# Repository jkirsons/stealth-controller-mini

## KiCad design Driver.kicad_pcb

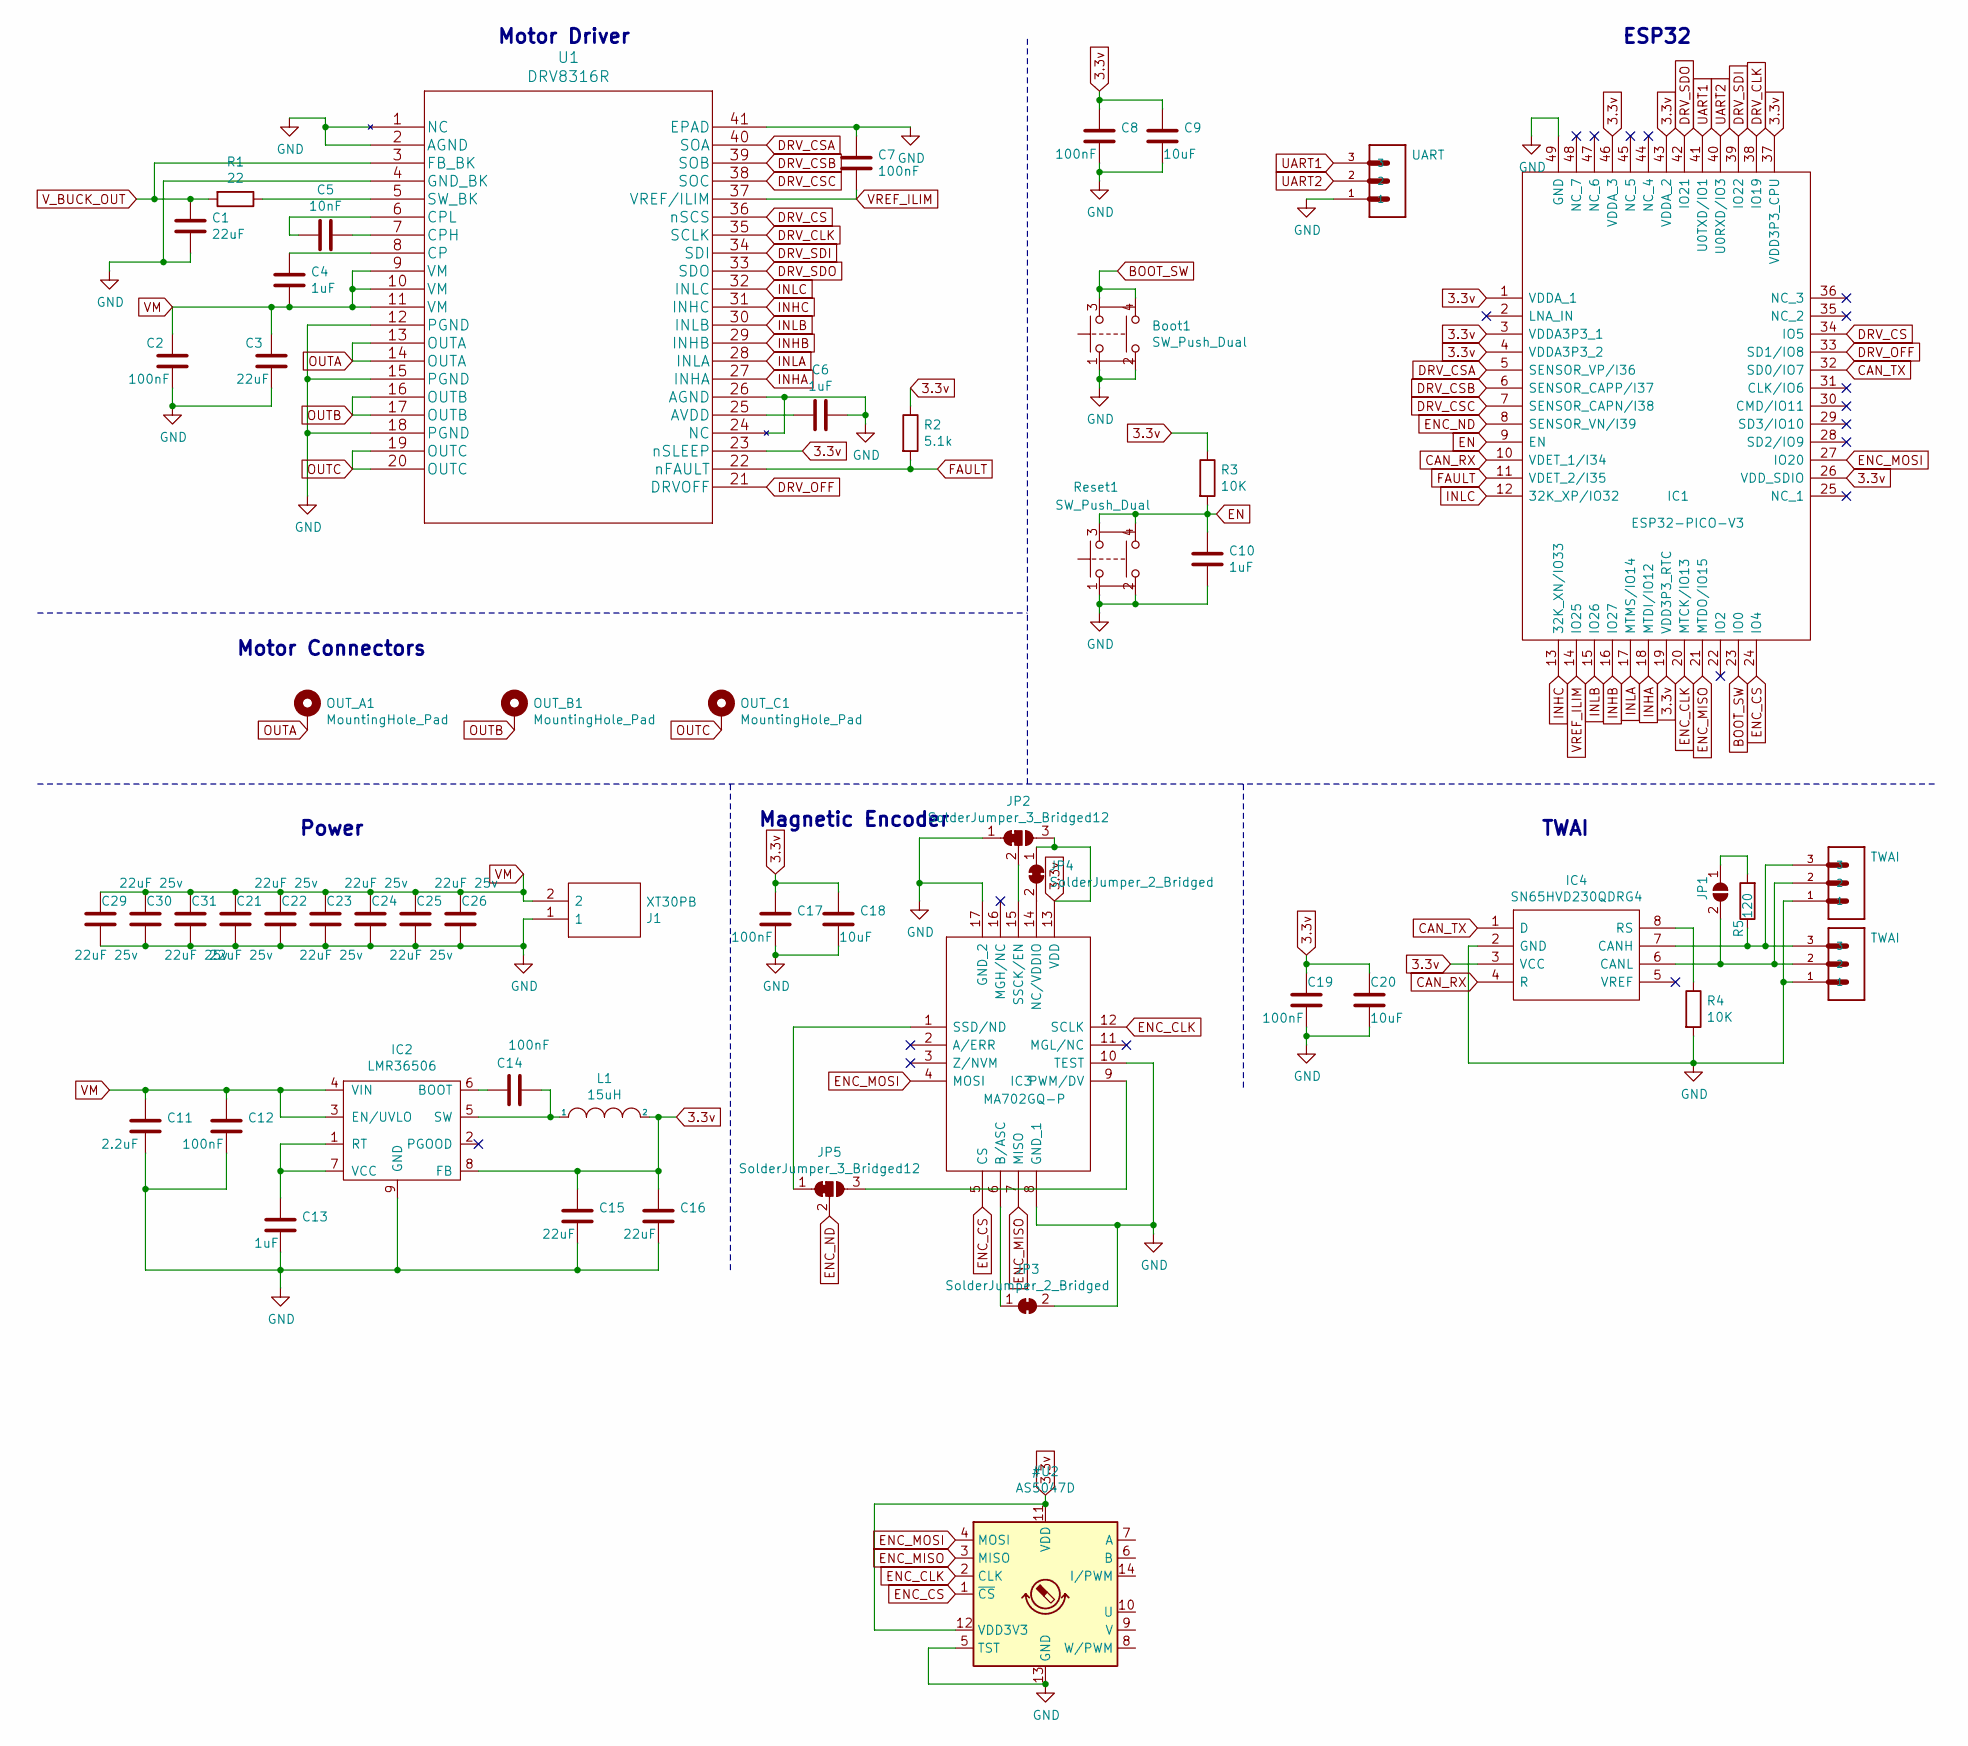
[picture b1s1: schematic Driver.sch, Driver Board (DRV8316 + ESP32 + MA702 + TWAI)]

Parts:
Boot1: SW_Push_Dual; XKB_Connectivity_TS-1177-B-B-B
C1, C15, C16: 22uF; C_0603_1608Metric
C2, C7, C8, C12, C14, C17, C19: 100nF; C_0603_1608Metric
C3: 22uF; C_0805_2012Metric
C4, C6, C10, C13: 1uF; C_0603_1608Metric
C5: 10nF; C_0603_1608Metric
C9, C18, C20: 10uF; C_0603_1608Metric
C11: 2.2uF; C_0603_1608Metric
C21, C22, C23, C24, C25, C26, C29, C30, C31: 22uF 25v; C_0805_2012Metric
IC1: ESP32-PICO-V3; ESP32PICOV3; Manufacturer_Part_Number ESP32-PICO-V3; Mouser Part Number 356-ESP32-PICO-V3
IC2: LMR36506
IC3: MA702GQ-P; MA702; Manufacturer_Part_Number MA702GQ-P; Mouser Part Number 946-MA702GQ-P
IC4: SN65HVD230QDRG4; SN65HVD230QDR; Manufacturer_Part_Number SN65HVD230QDRG4; Mouser Part Number 595-SN65HVD230QDRG4
J1: XT30PB; Manufacturer_Part_Number XT30PB
JP1: SolderJumper_2_Open; SolderJumper-2_P1.3mm_Open_RoundedPad1.0x1.5mm
JP2, JP5: SolderJumper_3_Bridged12; SolderJumper-3_P1.3mm_Open_RoundedPad1.0x1.5mm_NumberLabels
JP3, JP4: SolderJumper_2_Bridged; SolderJumper-2_P1.3mm_Open_RoundedPad1.0x1.5mm
L1: 15uH; L_1210_3225Metric; MPN NLCV32T-470K-PF; LCSC C83083
OUT_A1: MountingHole_Pad; Motor_Wire_Solder_Pad
OUT_B1: MountingHole_Pad; Motor_Wire_Solder_Pad
OUT_C1: MountingHole_Pad; Motor_Wire_Solder_Pad
R1: 22; R_0603_1608Metric
R2: 5.1k; R_0603_1608Metric
R3, R4: 10K; R_0603_1608Metric
R5: 120; R_0603_1608Metric
Reset1: SW_Push_Dual; XKB_Connectivity_TS-1177-B-B-B
TWAI1, TWAI2: TWAI; SHDR3W50P0X150
U1: DRV8316R; DRV8316
UART1: UART; SHDR3W50P0X150

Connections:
BOOT_SW: Boot1.3, Boot1.4, IC1.23 (IO0)
CAN_RX: IC1.10 (VDET_1/I34), IC4.4 (R)
CAN_TX: IC1.32 (SD0/IO7), IC4.1 (D)
DRV_CLK: IC1.38 (IO19), U1.35 (SCLK)
DRV_CS: IC1.34 (IO5), U1.36 (nSCS)
DRV_CSA: IC1.5 (SENSOR_VP/I36), U1.40 (SOA)
DRV_CSB: IC1.6 (SENSOR_CAPP/I37), U1.39 (SOB)
DRV_CSC: IC1.7 (SENSOR_CAPN/I38), U1.38 (SOC)
DRV_OFF: IC1.33 (SD1/IO8), U1.21 (DRVOFF)
DRV_SDI: IC1.39 (IO22), U1.34 (SDI)
DRV_SDO: IC1.42 (IO21), U1.33 (SDO)
EN: C10.1, IC1.9 (EN), R3.2, Reset1.3, Reset1.4
ENC_ND: IC1.8 (SENSOR_VN/I39), JP5.2 (C)
FAULT: IC1.11 (VDET_2/I35), R2.2, U1.22 (nFAULT)
INHA: IC1.18 (MTDI/IO12), U1.27 (INHA)
INHB: IC1.16 (IO27), U1.29 (INHB)
INHC: IC1.13 (32K_XN/IO33), U1.31 (INHC)
INLA: IC1.17 (MTMS/IO14), U1.28 (INLA)
INLB: IC1.15 (IO26), U1.30 (INLB)
INLC: IC1.12 (32K_XP/IO32), U1.32 (INLC)
unnamed: C4.1, U1.8 (CP)
unnamed: C5.1, U1.7 (CPH)
unnamed: C5.2, U1.6 (CPL)
unnamed: C6.2, U1.25 (AVDD)
unnamed: C13.1, IC2.1 (RT), IC2.7 (VCC)
unnamed: C14.1, IC2.6 (BOOT)
unnamed: C14.2, IC2.5 (SW), L1.1
unnamed: IC3.1 (SSD/ND), JP5.1 (A)
unnamed: IC3.6 (B/ASC), JP3.1 (A)
unnamed: IC3.9 (PWM/DV), JP5.3 (B)
unnamed: IC3.14 (NC/VDDIO), JP4.2 (B)
unnamed: IC3.15 (SSCK/EN), JP2.2 (C)
unnamed: IC4.6 (CANL), JP1.2 (B), TWAI1.2, TWAI2.2
unnamed: IC4.7 (CANH), R5.1, TWAI1.3, TWAI2.3
unnamed: IC4.8 (RS), R4.1
unnamed: JP1.1 (A), R5.2
unnamed: R1.1, U1.5 (SW_BK)
OUTA: OUT_A1.1, U1.13 (OUTA), U1.14 (OUTA)
OUTB: OUT_B1.1, U1.16 (OUTB), U1.17 (OUTB)
OUTC: OUT_C1.1, U1.19 (OUTC), U1.20 (OUTC)
UART1: IC1.41 (U0TXD/IO1), UART1.3
UART2: IC1.40 (U0RXD/IO3), UART1.2
VM: C2.1, C3.1, C4.2, C11.1, C12.1, C21.1, C22.1, C23.1, C24.1, C25.1, C26.1, C29.1, C30.1, C31.1, IC2.3 (EN/UVLO), IC2.4 (VIN), J1.2, U1.9 (VM), U1.10 (VM), U1.11 (VM)
VREF_ILIM: C7.2, IC1.14 (IO25), U1.37 (VREF/ILIM)
V_BUCK_OUT: C1.1, R1.2, U1.3 (FB_BK)

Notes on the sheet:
Motor Driver
Motor Connectors
ESP32
Magnetic Encoder
TWAI
Power

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
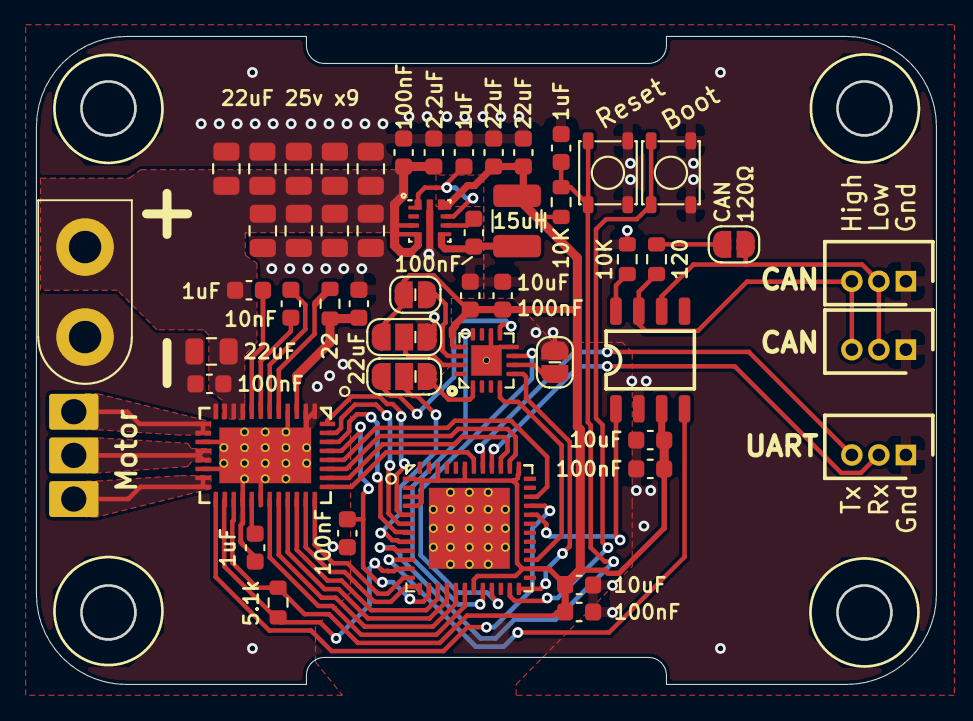
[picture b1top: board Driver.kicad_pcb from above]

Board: 2 copper layers, 50.0 x 36.0 mm, 54 parts (0 on the bottom side), 51 nets.

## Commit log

2022-05-25 Create LICENSE
2022-05-25 Remove license

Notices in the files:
Driver.sch:
MIT License
